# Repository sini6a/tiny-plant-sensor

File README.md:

# Tiny Plant Sensor 🌱

The Tiny Plant Sensor 🌱 is a low-power sensor designed around the Attiny85 microcontroller and powered by a CR2032 coin cell battery. This sensor is designed to monitor the moisture level of a plant and provide a visual indication when watering is required.

## Features

- Utilizes Attiny85 microcontroller
- Powered by CR2032 coin cell battery
- Monitors plant moisture using capacitance level
- Sleeps and wakes up every 6 seconds for power efficiency
- Blinking LED indicates the need for watering

## Operation

The sensor operates by periodically waking up to check the plant's capacitance level, determining if watering is necessary. If the plant requires watering, the sensor activates a blinking LED every second. Otherwise, it remains in a low-power state.

## Usage

Simply deploy the Tiny Plant Sensor in the vicinity of the plant you wish to monitor. Ensure the CR2032 battery is properly inserted, and the sensor will autonomously manage its sleep-wake cycles to conserve power while providing visual cues for watering needs.

Feel free to customize and adapt the Tiny Plant Sensor for your specific plant monitoring requirements.

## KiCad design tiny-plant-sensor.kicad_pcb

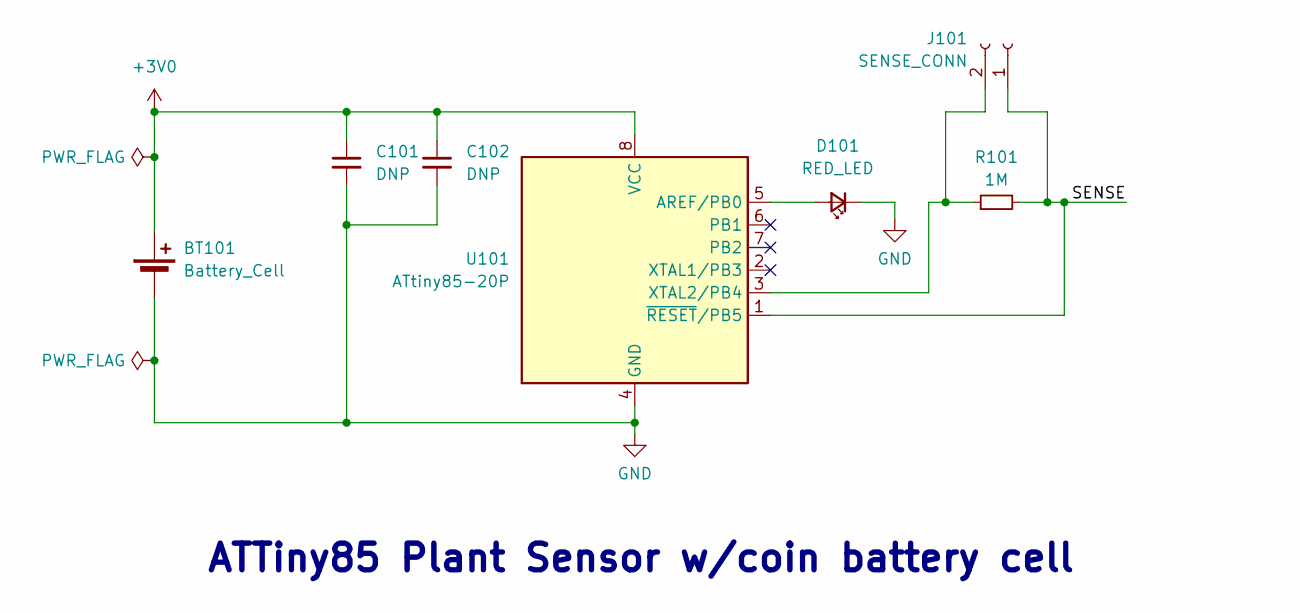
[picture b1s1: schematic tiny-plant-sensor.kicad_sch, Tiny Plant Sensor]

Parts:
BT101: Battery_Cell; BatteryHolder_Keystone_103_1x20mm
C101: DNP; C_0805_2012Metric_Pad1.18x1.45mm_HandSolder
C102: DNP; C_0603_1608Metric_Pad1.08x0.95mm_HandSolder
D101: RED_LED; LED_D3.0mm
J101: SENSE_CONN; SolderWire-0.5sqmm_1x02_P4.6mm_D0.9mm_OD2.1mm
R101: 1M; R_Axial_DIN0204_L3.6mm_D1.6mm_P5.08mm_Horizontal
U101: ATtiny85-20P; DIP-8_W7.62mm_Socket

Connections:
+3V0: BT101.1 (+), C101.1, C102.1, U101.8 (VCC)
/SENSE: J101.1, R101.2, U101.1 (~RESET/PB5)
GND: BT101.2 (-), C101.2, C102.2, D101.1 (K), U101.4 (GND)
unnamed: D101.2 (A), U101.5 (AREF/PB0)
unnamed: J101.2, R101.1, U101.3 (XTAL2/PB4)

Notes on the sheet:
ATTiny85 Plant Sensor w/coin battery cell

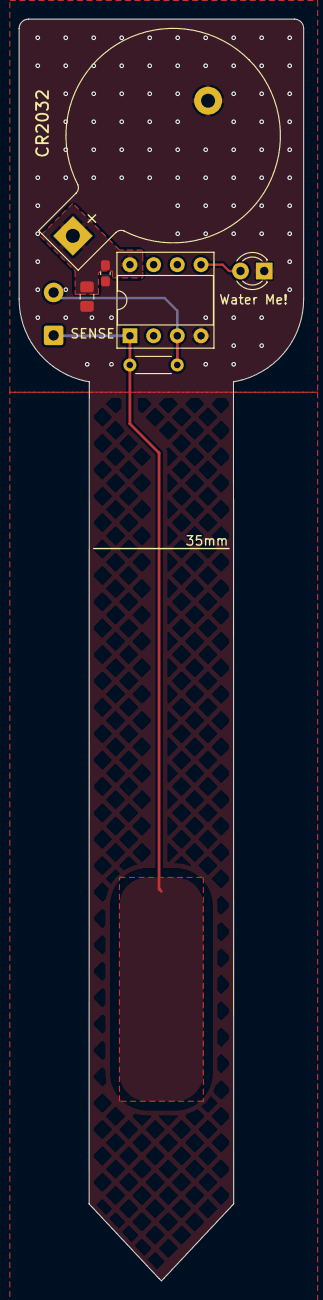
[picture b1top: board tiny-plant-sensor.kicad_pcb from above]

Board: 2 copper layers, 30.5 x 135.2 mm, 7 parts (0 on the bottom side), 5 nets.

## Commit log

2024-02-13 revision 1
2024-02-13 added readme
